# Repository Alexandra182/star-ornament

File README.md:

# star-ornament

★ Tiny Star PCB ornament designed for the [JLCPCB](https://jlcpcb.com/) design contest.

Details here:

https://hackaday.io/project/177787-attiny13a-pcb-star-wearable

https://www.hackster.io/alexandracovor/attiny13a-pcb-star-wearable-63ce67

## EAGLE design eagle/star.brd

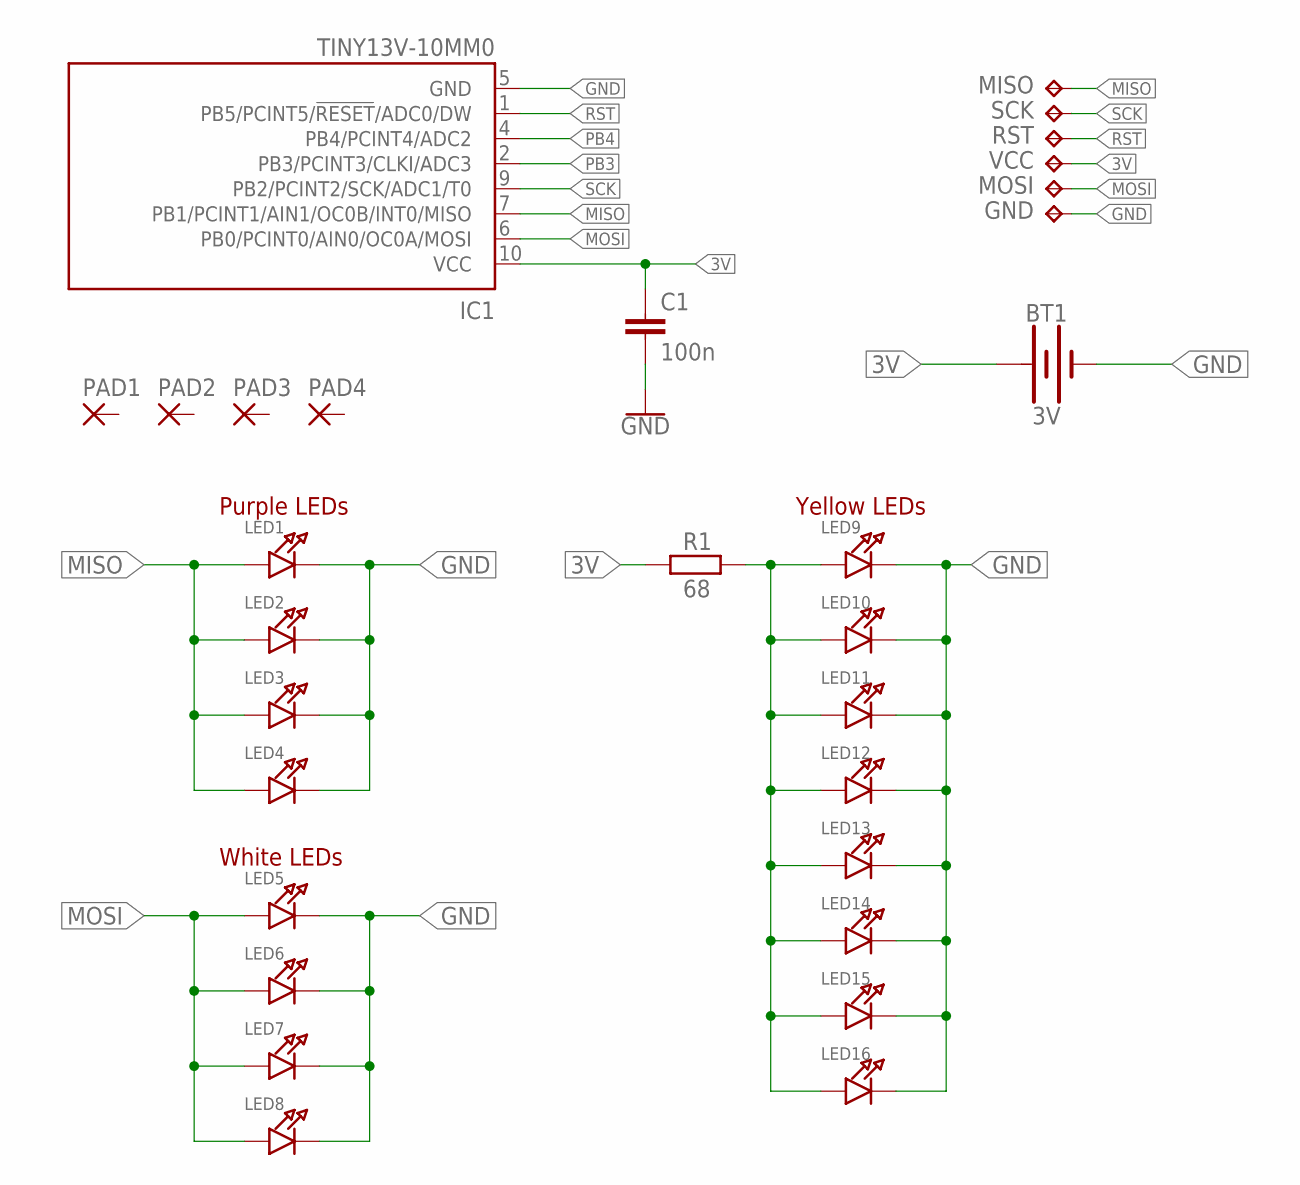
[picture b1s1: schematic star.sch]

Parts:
BT1: 3V; BATTCON_12MM
C1: 100n; C0603K
GND: TPB1,27; B1,27
IC1: TINY13V-10MM0; 10M1
LED1, LED2, LED3, LED4, LED5, LED6, LED7, LED8, LED9, LED10, LED11, LED12, LED13, LED14, LED15, LED16: LED0603_NOOUTLINE; CHIPLED_0603_NOOUTLINE
MISO: TPB1,27; B1,27
MOSI: TPB1,27; B1,27
PAD1, PAD2, PAD3, PAD4: SMD2; SMD1,27-2,54
R1: 68; R0603
RST: TPB1,27; B1,27
SCK: TPB1,27; B1,27
VCC: TPB1,27; B1,27

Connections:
3V: BT1.PWR@2 (+), C1.1, IC1.10 (VCC), R1.1, VCC.TP
GND: BT1.GND (-), C1.2, GND.TP, IC1.5 (GND), IC1.11 (GND), LED1.C, LED2.C, LED3.C, LED4.C, LED5.C, LED6.C, LED7.C, LED8.C, LED9.C, LED10.C, LED11.C, LED12.C, LED13.C, LED14.C, LED15.C, LED16.C
MISO: IC1.7 (PB1/PCINT1/AIN1/OC0B/INT0/MISO), LED1.A, LED2.A, LED3.A, LED4.A, MISO.TP
MOSI: IC1.6 (PB0/PCINT0/AIN0/OC0A/MOSI), LED5.A, LED6.A, LED7.A, LED8.A, MOSI.TP
PB3: IC1.2 (PB3/PCINT3/CLKI/ADC3)
PB4: IC1.4 (PB4/PCINT4/ADC2)
RES: LED9.A, LED10.A, LED11.A, LED12.A, LED13.A, LED14.A, LED15.A, LED16.A, R1.2
RST: IC1.1 (PB5/PCINT5/!RESET!/ADC0/DW), RST.TP
SCK: IC1.9 (PB2/PCINT2/SCK/ADC1/T0), SCK.TP

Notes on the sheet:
Purple LEDs
Yellow LEDs
White LEDs

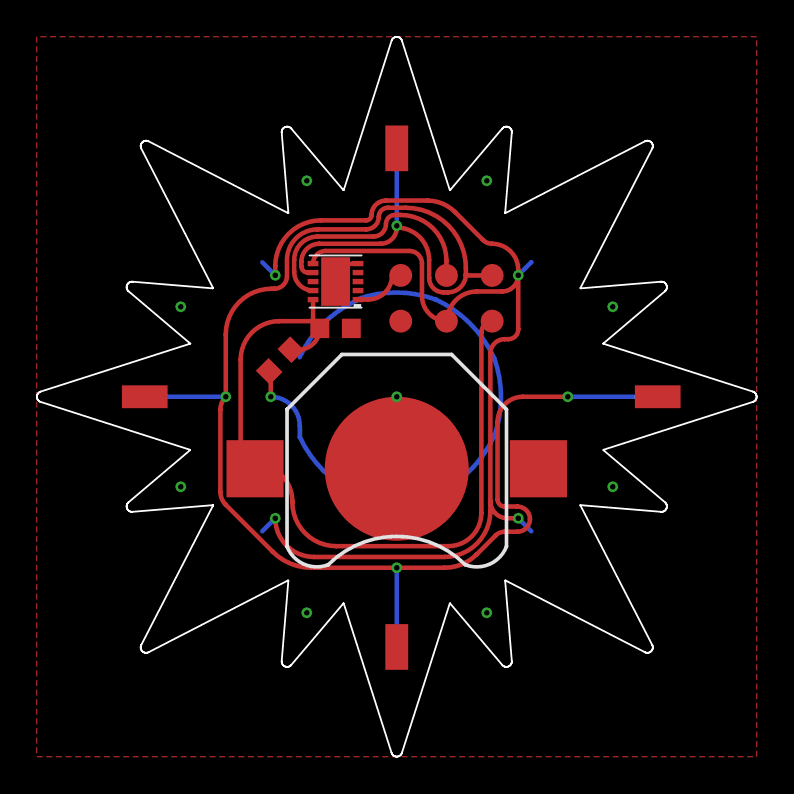
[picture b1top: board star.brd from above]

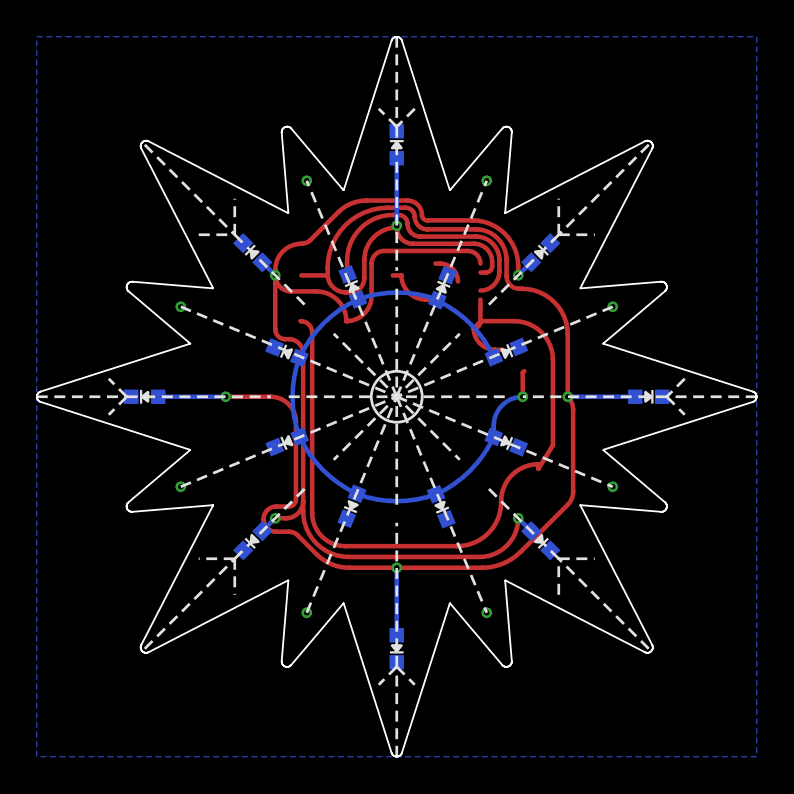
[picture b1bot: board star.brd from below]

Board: 2 copper layers, 40.0 x 40.0 mm, 30 parts (16 on the bottom side), 7 nets.

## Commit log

2020-12-22 images
2020-12-22 arduino code
2021-02-20 small code updates, cleanup
2021-04-09 added gerber files

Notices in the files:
parts and their libraries:
SparkFun-Batteries: Licensing: Creative Commons ShareAlike 4.0 International - https://creativecommons.org/licenses/by-sa/4.0
microbuilder: This work is placed in the public domain, and may be freely used for commercial and non-commercial work with the following conditions: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
